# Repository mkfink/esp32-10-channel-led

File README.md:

ESP32-based 10-Channel LED controller for WS2815 or similar
* Designed to run WLED
* Powerpole or barrel jack compatible

BOM
* ESP32-WROOM-32D
* AMS1117 3.3v regulator
* Surface mount JST-XH right angle connectors
* Surface mount components (5K & 12K resistors, 100nf cap)
* 3 pin barrel jack or board mount power pole (1377G1-BK) connectors

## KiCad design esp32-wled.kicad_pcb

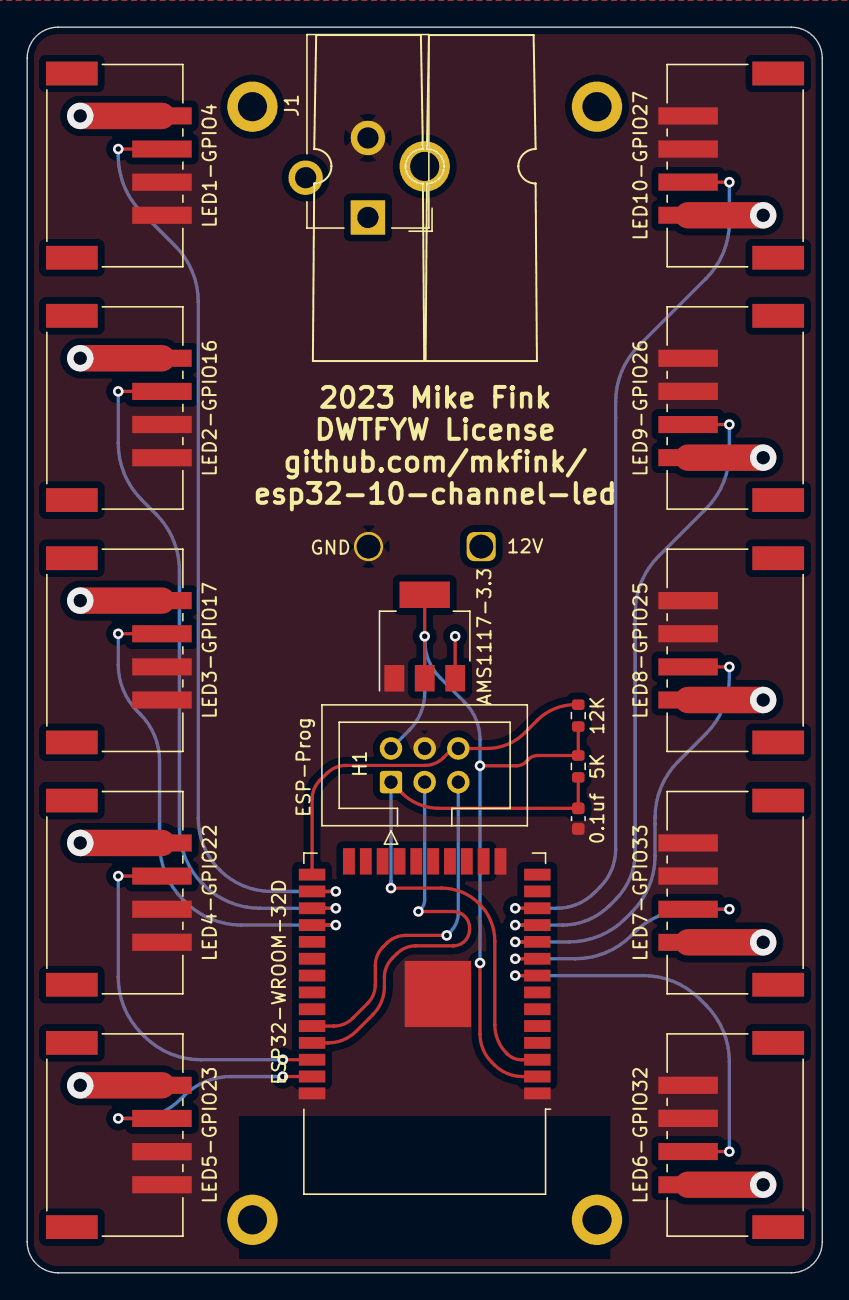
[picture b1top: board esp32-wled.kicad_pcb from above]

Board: 2 copper layers, 60.0 x 94.0 mm, 24 parts (0 on the bottom side), 17 nets.

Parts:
12V: Conn_01x01; Anderson_Powerpole-25A-RA-G1
 : MountingHole_2.2mm_M2_DIN965_Pad
 #2,  #3,  #4,  #5: MountingHole_2.2mm_M2_DIN965_Pad
C1: 0.1uf; C_0603_1608Metric
GND: Conn_01x01; Anderson_Powerpole-25A-RA-G1
H1: ESP32Header; IDC-Header_2x03_P2.54mm_Vertical
J1: Barrel_Jack; BarrelJack_CUI_PJ-102AH_Horizontal
LED1-GPIO4, LED2-GPIO16, LED3-GPIO17, LED4-GPIO22, LED5-GPIO23, LED6-GPIO32, LED7-GPIO33, LED8-GPIO25, LED9-GPIO26, LED10-GPIO27: Conn_01x04; S4B-XH-SM4-TBLFSN
R1: 12K; R_0603_1608Metric
R2: 5K; R_0603_1608Metric
U1: ESP32-WROOM-32D; ESP32-WROOM-32
U2: AMS1117-3.3; SOT-223-3_TabPin2

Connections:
+3.3V: H1.2, R1.2, R2.1, U1.2 (VDD), U2.2 (VO)
+12V: 12V.1, J1.1, LED1-GPIO4.1, LED2-GPIO16.1, LED3-GPIO17.1, LED4-GPIO22.1, LED5-GPIO23.1, LED6-GPIO32.1, LED7-GPIO33.1, LED8-GPIO25.1, LED9-GPIO26.1, LED10-GPIO27.1, U2.3 (VI)
EN: C1.2, H1.1, R2.2, U1.3 (EN)
GND: C1.1, GND.1, H1.4, J1.2, LED1-GPIO4.3, LED1-GPIO4.4, LED2-GPIO16.3, LED2-GPIO16.4, LED3-GPIO17.3, LED3-GPIO17.4, LED4-GPIO22.3, LED4-GPIO22.4, LED5-GPIO23.3, LED5-GPIO23.4, LED6-GPIO32.3, LED6-GPIO32.4, LED7-GPIO33.3, LED7-GPIO33.4, LED8-GPIO25.3, LED8-GPIO25.4, LED9-GPIO26.3, LED9-GPIO26.4, LED10-GPIO27.3, LED10-GPIO27.4, U1.1 (GND), U1.15 (GND), U1.38 (GND), U1.39 (GND), U2.1 (GND)
GPIO0: H1.6, R1.1, U1.25 (IO0)
unnamed: LED1-GPIO4.2, U1.26 (IO4)
unnamed: LED2-GPIO16.2, U1.27 (IO16)
unnamed: LED3-GPIO17.2, U1.28 (IO17)
unnamed: LED4-GPIO22.2, U1.36 (IO22)
unnamed: LED5-GPIO23.2, U1.37 (IO23)
unnamed: LED6-GPIO32.2, U1.8 (IO32)
unnamed: LED7-GPIO33.2, U1.9 (IO33)
unnamed: LED8-GPIO25.2, U1.10 (IO25)
unnamed: LED9-GPIO26.2, U1.11 (IO26)
unnamed: LED10-GPIO27.2, U1.12 (IO27)
RX: H1.5, U1.34 (RXD0/IO3)
TX: H1.3, U1.35 (TXD0/IO1)

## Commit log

2023-06-29 add readme
2023-06-29 add image

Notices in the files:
parts and their libraries:
Copyright 2021 Accelerated Designs. All rights reserved.
